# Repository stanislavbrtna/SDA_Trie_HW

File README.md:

# SDA Trié Hardware Sources
Trié is third iteration of the SDA design, it tries to merge the form factor of Sony Clié V-body and phone functionality of the Palm Treo devices, so Trié. In the pcb directory are KiCad project files for the Boards used in the SDA. In the case Directory there are FreeCAD files for the SDA case. You can find more info about the SDA Project on its [project page](https://hackaday.io/project/35165-sda-the-best-new-pda) on hackaday.io.

This design is work-in-progress.

## Known Bugs

## Case notes

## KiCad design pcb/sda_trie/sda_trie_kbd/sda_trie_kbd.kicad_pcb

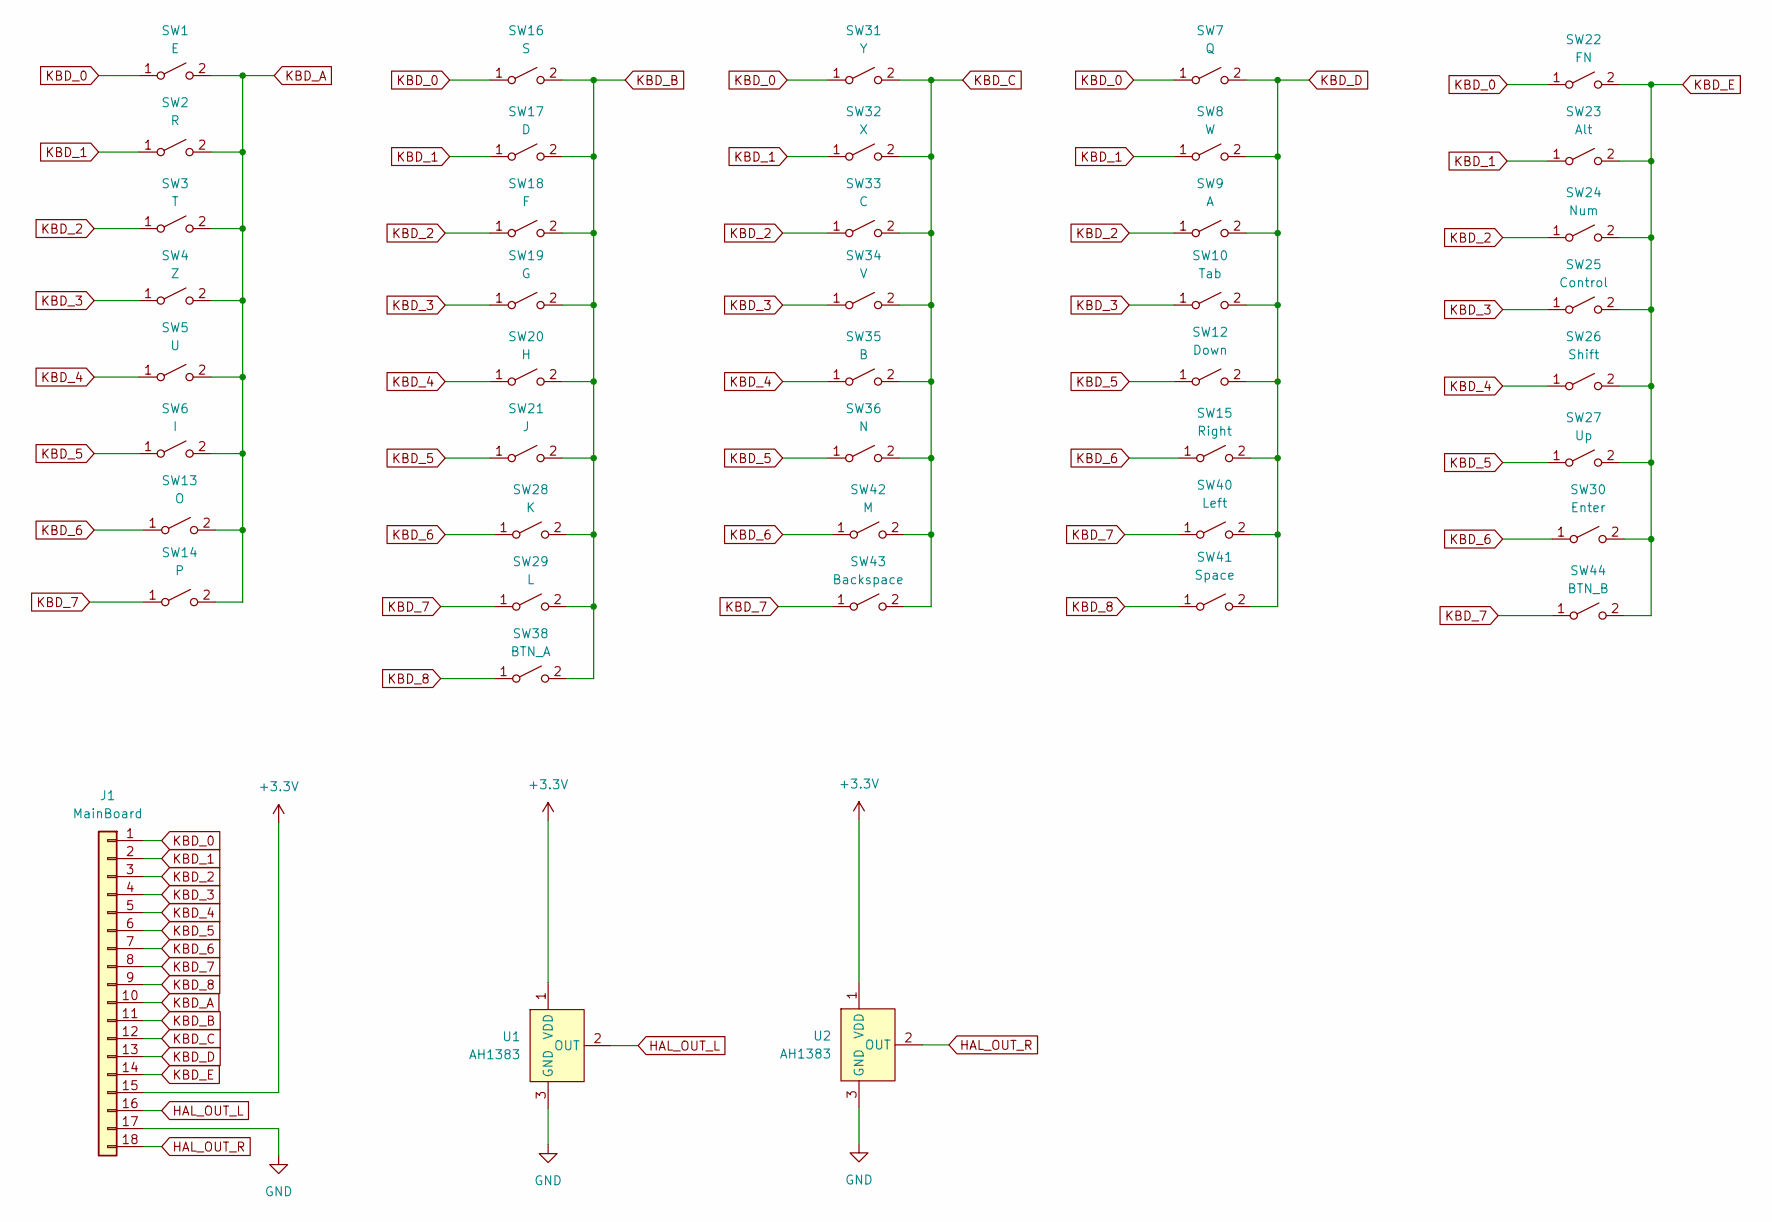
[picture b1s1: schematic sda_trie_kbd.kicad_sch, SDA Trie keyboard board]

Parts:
J1: MainBoard; TE_1-1734839-8_1x18-1MP_P0.5mm_Horizontal
SW1: E; TACT_4MM
SW2: R; TACT_4MM
SW3: T; TACT_4MM
SW4: Z; TACT_4MM
SW5: U; TACT_4MM
SW6: I; TACT_4MM
SW7: Q; TACT_4MM
SW8: W; TACT_4MM
SW9: A; TACT_4MM
SW10: Tab; TACT_4MM
SW12: Down; TACT_4MM
SW13: O; TACT_4MM
SW14: P; TACT_4MM
SW15: Right; TACT_4MM
SW16: S; TACT_4MM
SW17: D; TACT_4MM
SW18: F; TACT_4MM
SW19: G; TACT_4MM
SW20: H; TACT_4MM
SW21: J; TACT_4MM
SW22: FN; TACT_4MM
SW23: Alt; TACT_4MM
SW24: Num; TACT_4MM
SW25: Control; TACT_4MM
SW26: Shift; TACT_4MM
SW27: Up; TACT_4MM
SW28: K; TACT_4MM
SW29: L; TACT_4MM
SW30: Enter; TACT_4MM
SW31: Y; TACT_4MM
SW32: X; TACT_4MM
SW33: C; TACT_4MM
SW34: V; TACT_4MM
SW35: B; TACT_4MM
SW36: N; TACT_4MM
SW38: BTN_A; TACT_4MM
SW40: Left; TACT_4MM
SW41: Space; TACT_4MM
SW42: M; TACT_4MM
SW43: Backspace; TACT_4MM
SW44: BTN_B; TACT_4MM
U1, U2: AH1383; SOT-23

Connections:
+3.3V: J1.15, U1.1 (VDD), U2.1 (VDD)
GND: J1.17, U1.3 (GND), U2.3 (GND)
HAL_OUT_L: J1.16, U1.2 (OUT)
HAL_OUT_R: J1.18, U2.2 (OUT)
KBD_0: J1.1, SW1.1 (A), SW7.1 (A), SW16.1 (A), SW22.1 (A), SW31.1 (A)
KBD_1: J1.2, SW2.1 (A), SW8.1 (A), SW17.1 (A), SW23.1 (A), SW32.1 (A)
KBD_2: J1.3, SW3.1 (A), SW9.1 (A), SW18.1 (A), SW24.1 (A), SW33.1 (A)
KBD_3: J1.4, SW4.1 (A), SW10.1 (A), SW19.1 (A), SW25.1 (A), SW34.1 (A)
KBD_4: J1.5, SW5.1 (A), SW20.1 (A), SW26.1 (A), SW35.1 (A)
KBD_5: J1.6, SW6.1 (A), SW12.1 (A), SW21.1 (A), SW27.1 (A), SW36.1 (A)
KBD_6: J1.7, SW13.1 (A), SW15.1 (A), SW28.1 (A), SW30.1 (A), SW42.1 (A)
KBD_7: J1.8, SW14.1 (A), SW29.1 (A), SW40.1 (A), SW43.1 (A), SW44.1 (A)
KBD_8: J1.9, SW38.1 (A), SW41.1 (A)
KBD_A: J1.10, SW1.2 (B), SW2.2 (B), SW3.2 (B), SW4.2 (B), SW5.2 (B), SW6.2 (B), SW13.2 (B), SW14.2 (B)
KBD_B: J1.11, SW16.2 (B), SW17.2 (B), SW18.2 (B), SW19.2 (B), SW20.2 (B), SW21.2 (B), SW28.2 (B), SW29.2 (B), SW38.2 (B)
KBD_C: J1.12, SW31.2 (B), SW32.2 (B), SW33.2 (B), SW34.2 (B), SW35.2 (B), SW36.2 (B), SW42.2 (B), SW43.2 (B)
KBD_D: J1.13, SW7.2 (B), SW8.2 (B), SW9.2 (B), SW10.2 (B), SW12.2 (B), SW15.2 (B), SW40.2 (B), SW41.2 (B)
KBD_E: J1.14, SW22.2 (B), SW23.2 (B), SW24.2 (B), SW25.2 (B), SW26.2 (B), SW27.2 (B), SW30.2 (B), SW44.2 (B)

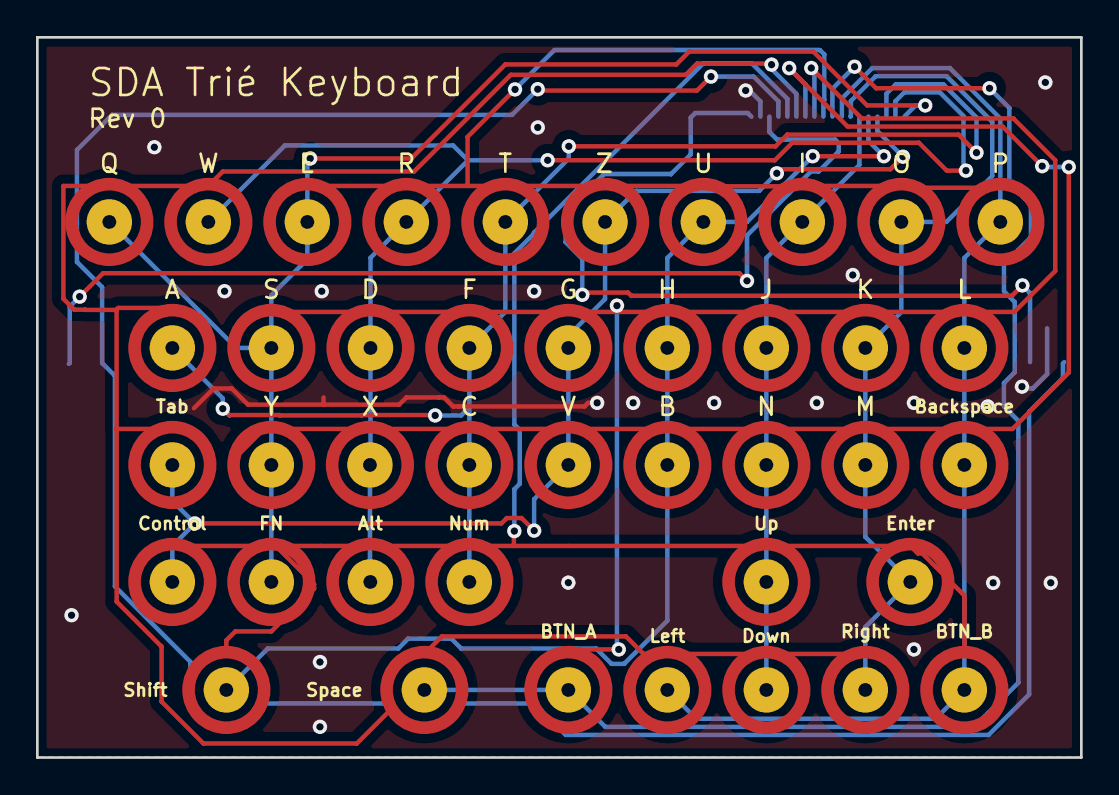
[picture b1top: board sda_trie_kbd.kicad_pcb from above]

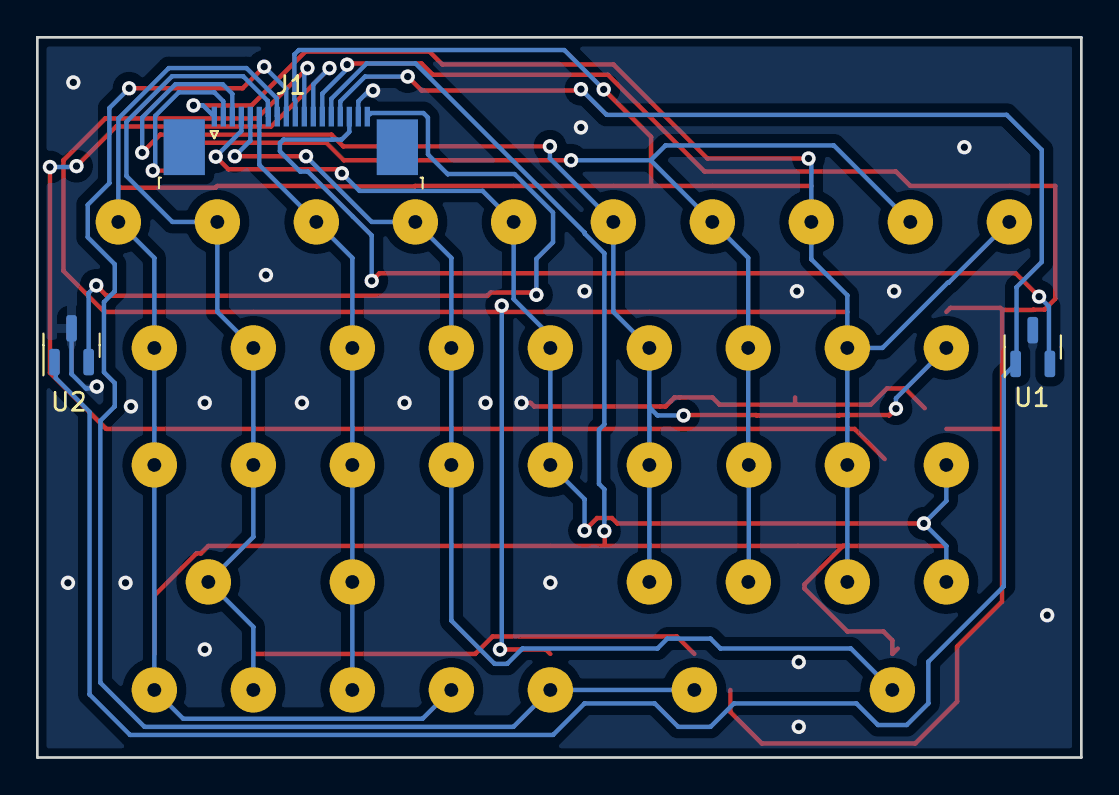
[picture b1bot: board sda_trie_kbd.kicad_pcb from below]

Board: 2 copper layers, 58.0 x 40.0 mm, 44 parts (3 on the bottom side), 18 nets.

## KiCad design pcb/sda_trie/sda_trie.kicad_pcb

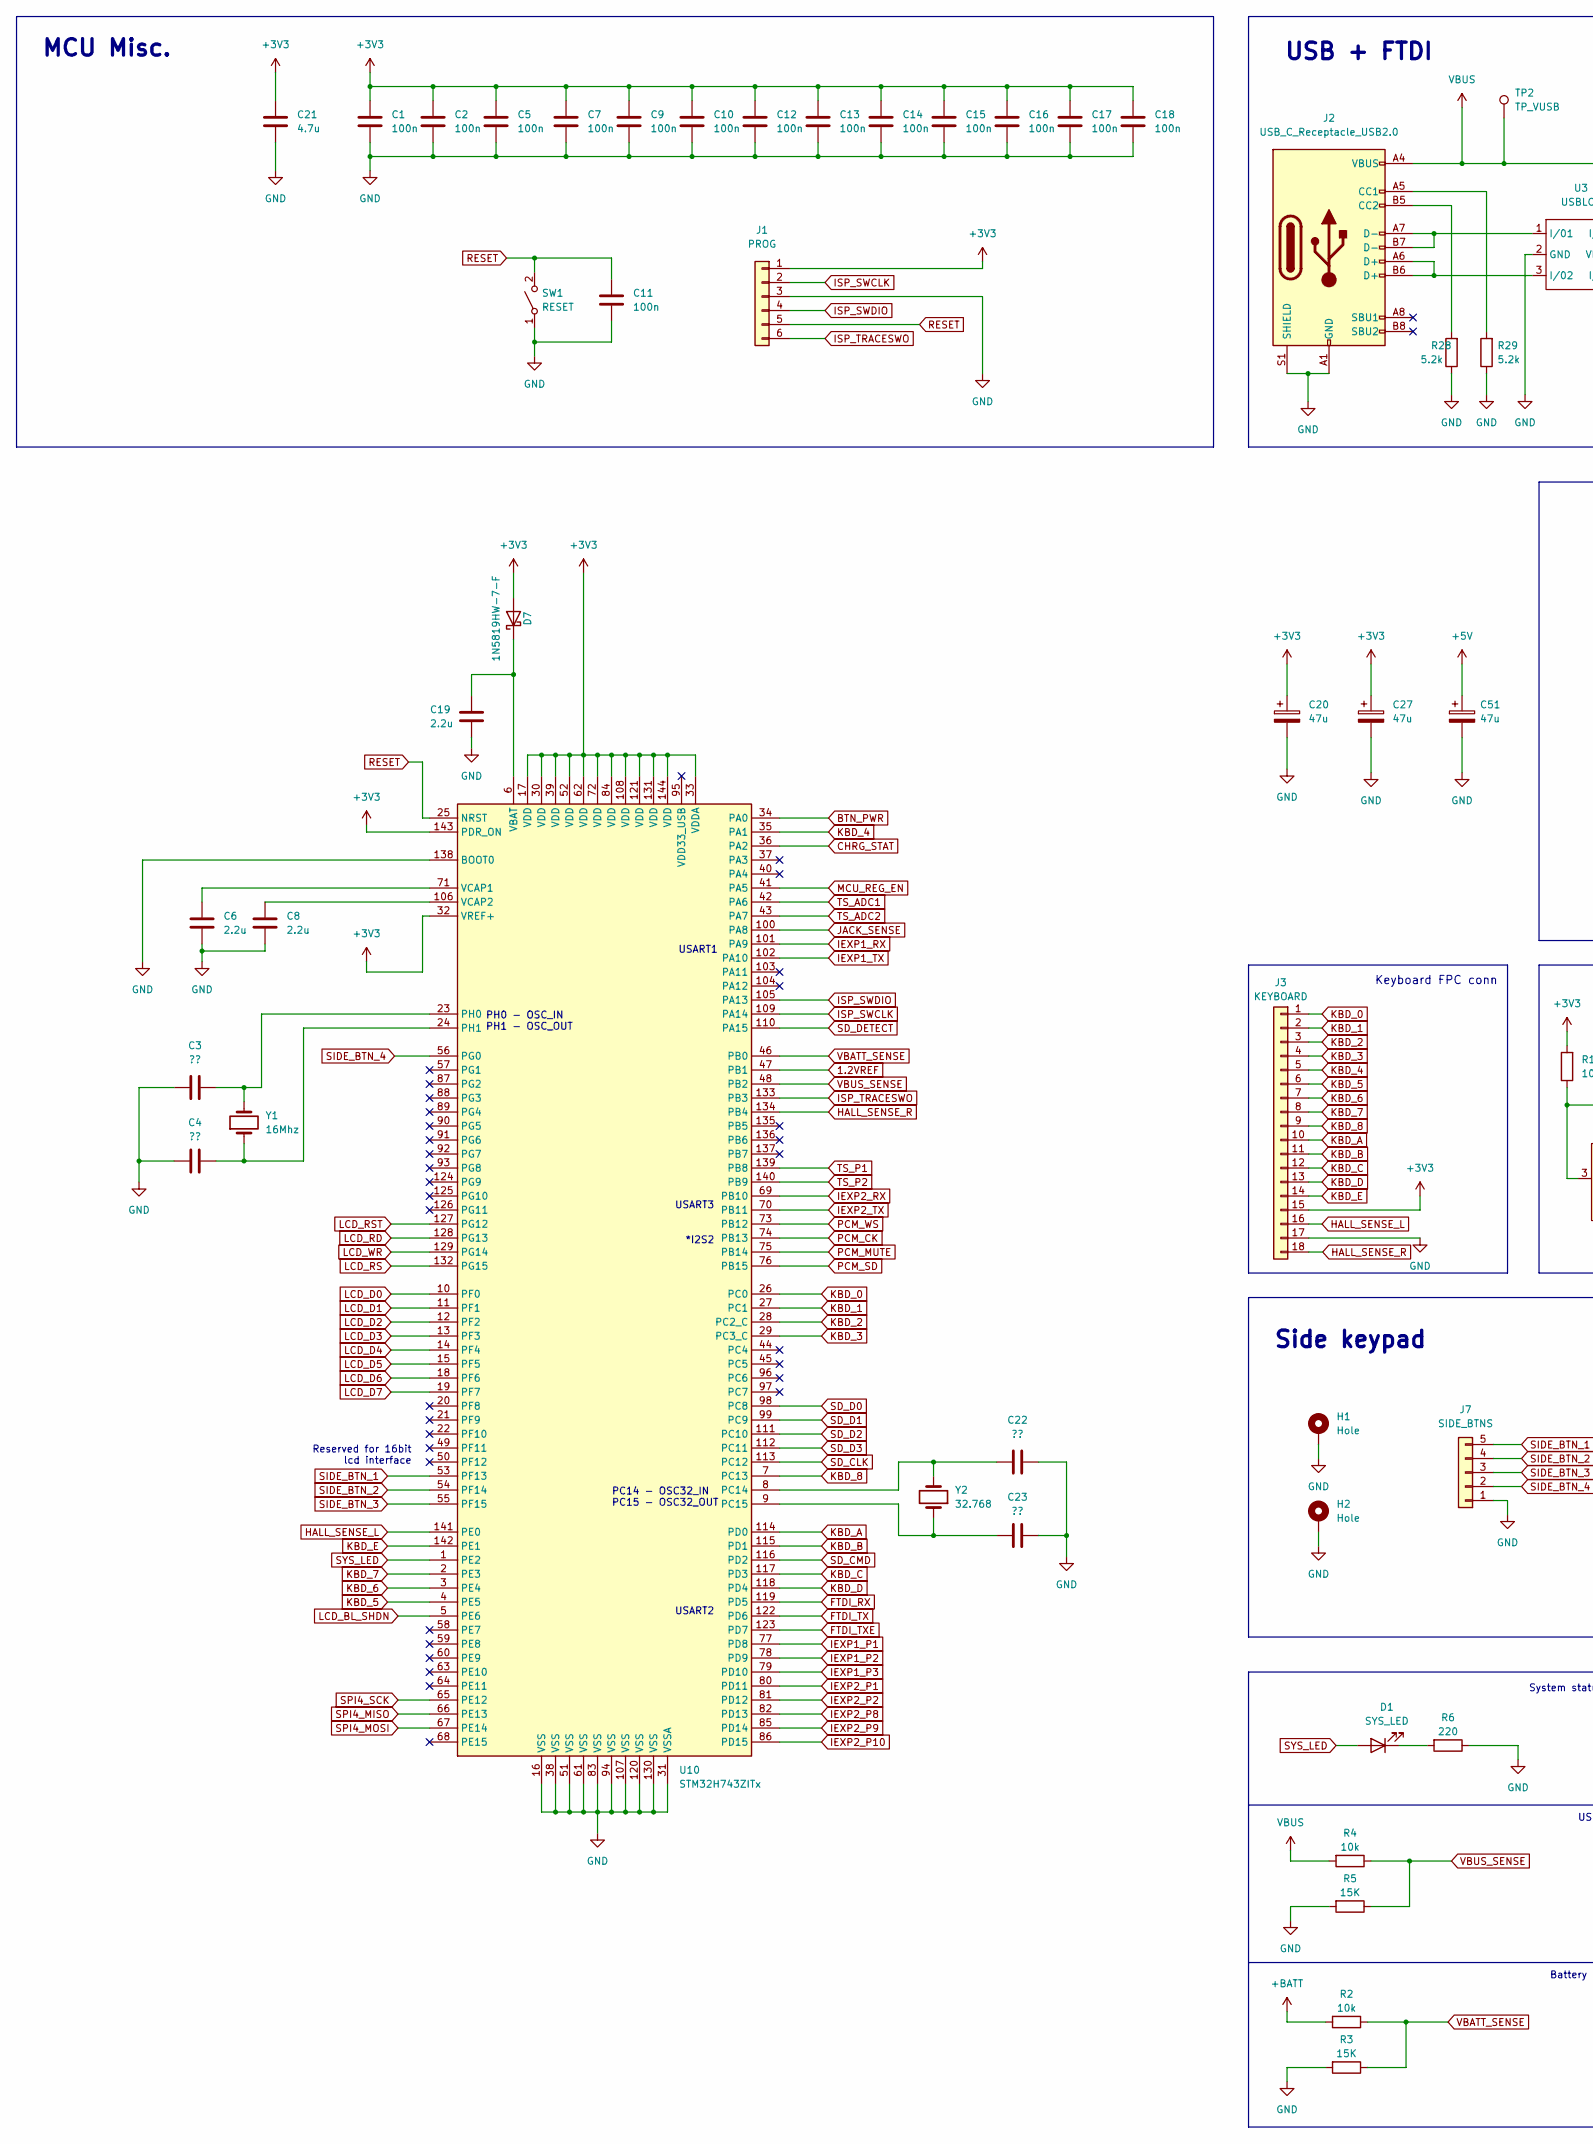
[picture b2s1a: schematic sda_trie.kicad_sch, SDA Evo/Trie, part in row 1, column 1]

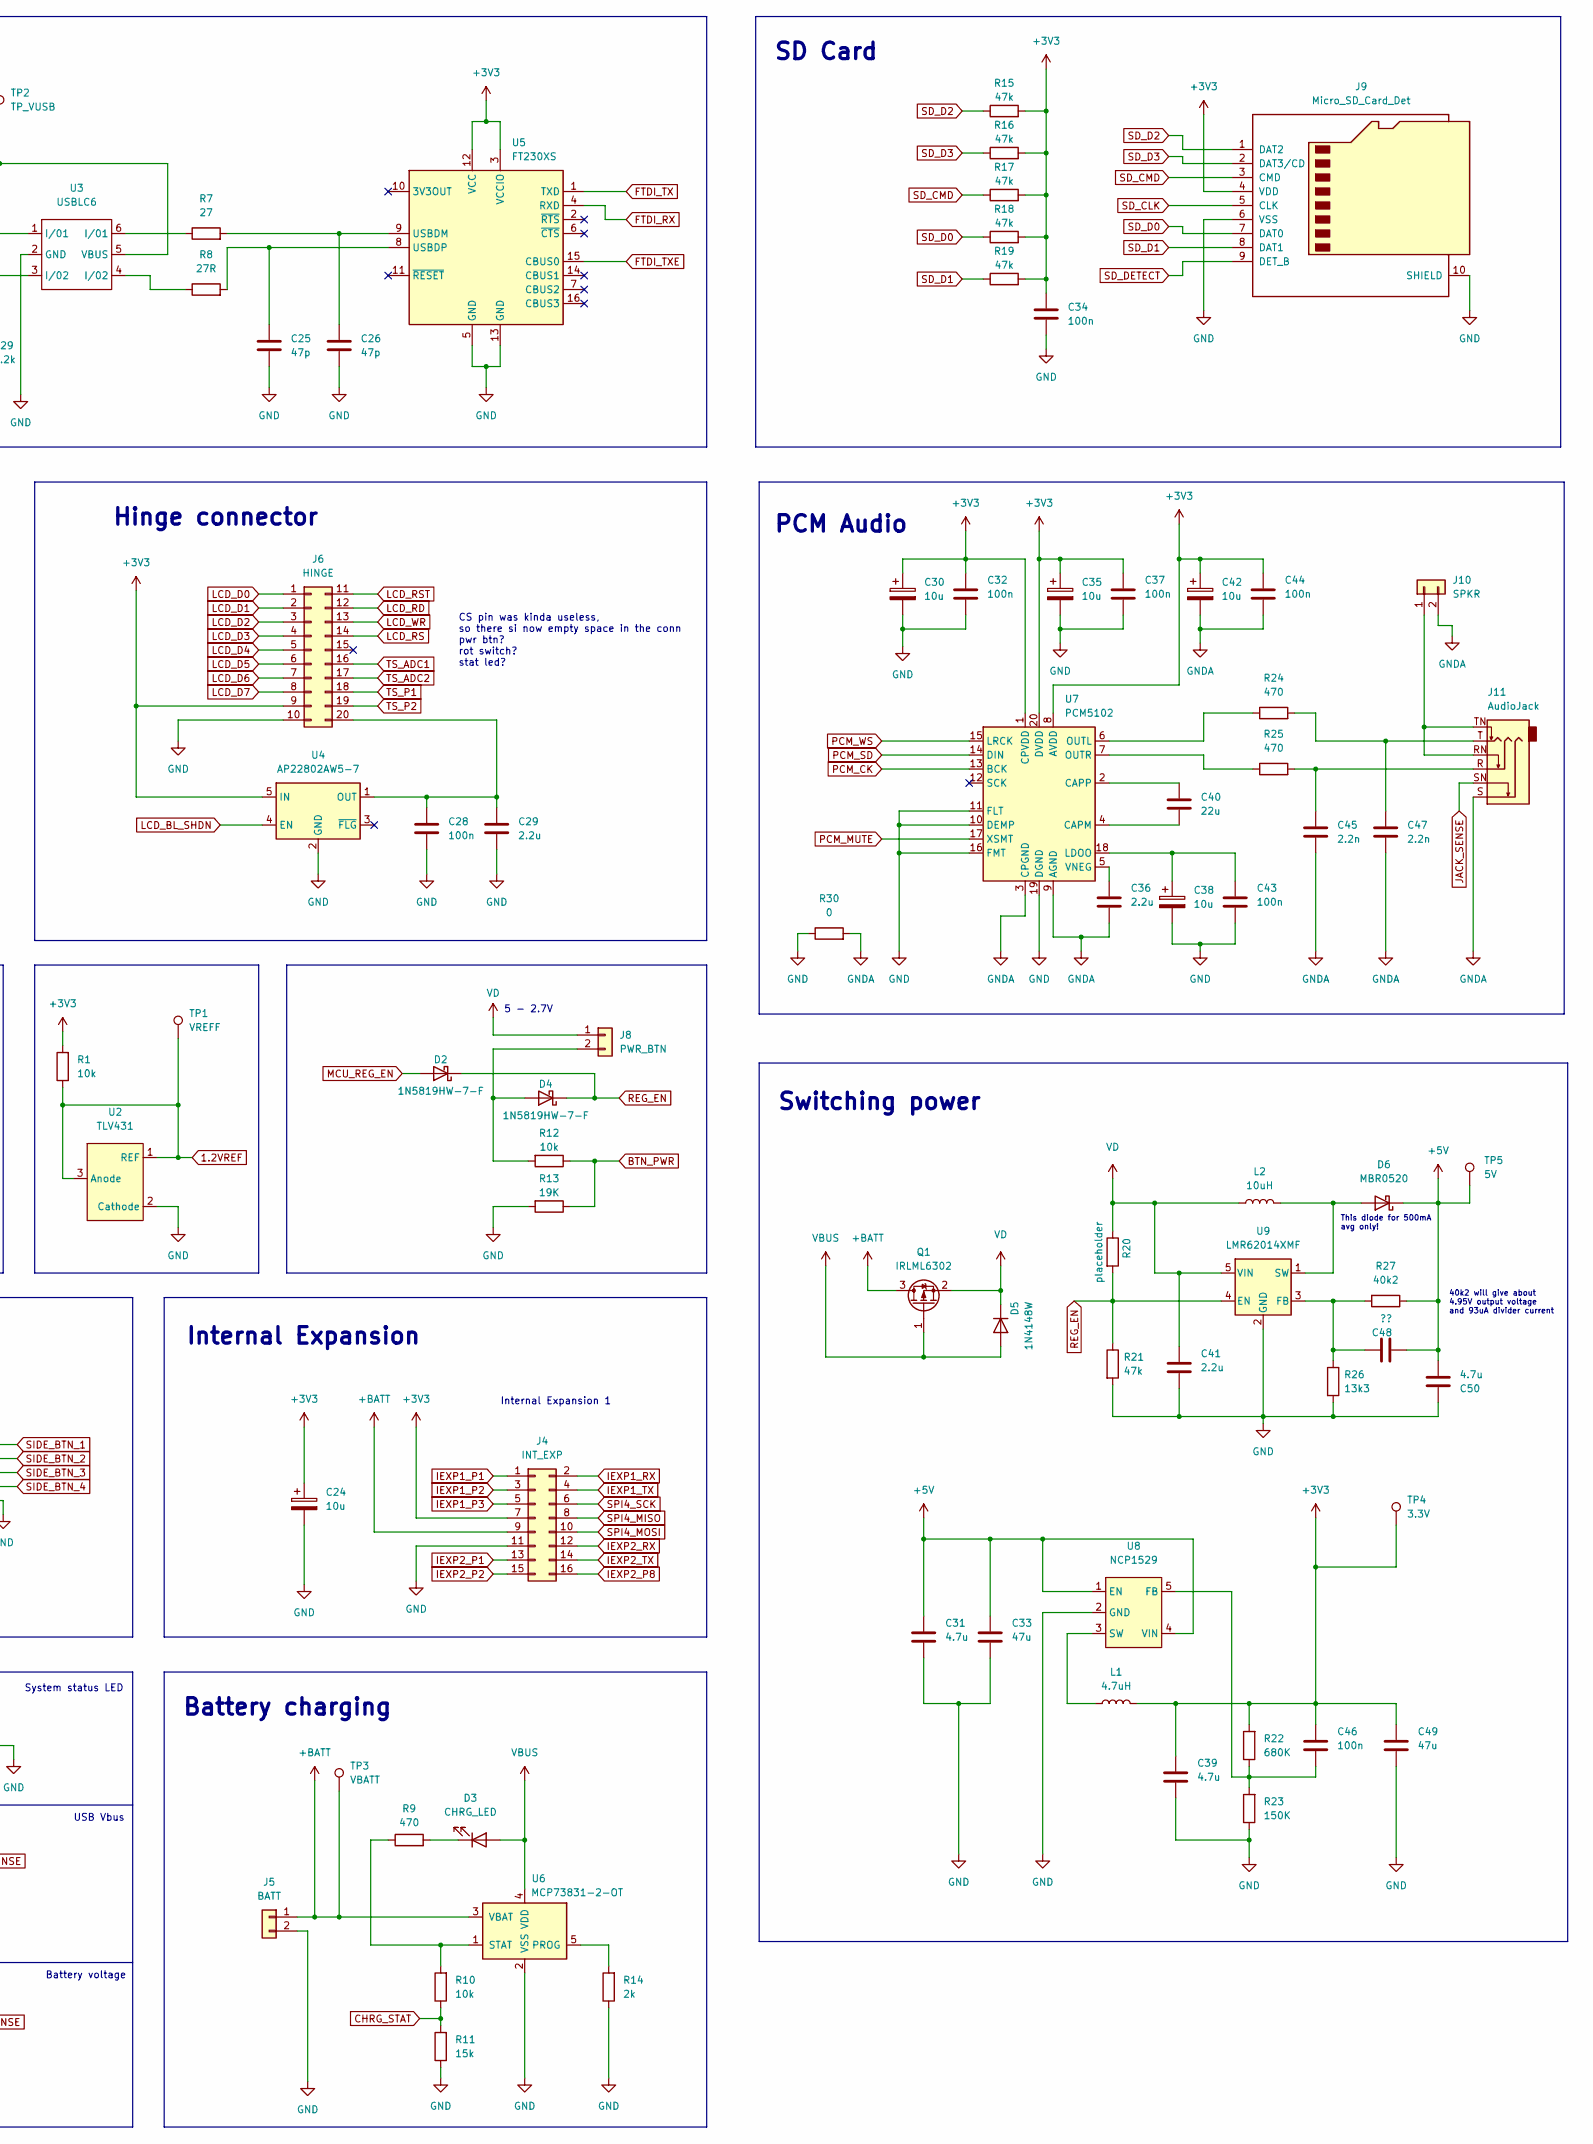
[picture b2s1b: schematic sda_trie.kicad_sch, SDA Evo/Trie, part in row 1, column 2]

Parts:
C1, C2, C5, C7, C9, C10, C11, C12, C13, C14, C15, C16, C17, C18, C28, C32, C34, C37, C43, C44, C46: 100n; C_0805_2012Metric_Pad1.18x1.45mm_HandSolder
C3, C4, C22, C23, C48: ??; C_0805_2012Metric_Pad1.18x1.45mm_HandSolder
C6, C8, C19, C29, C36, C41: 2.2u; C_0805_2012Metric_Pad1.18x1.45mm_HandSolder
C20, C27, C51: 47u; CP_EIA-7343-15_Kemet-W_Pad2.25x2.55mm_HandSolder
C21, C31, C39, C50: 4.7u; C_0805_2012Metric_Pad1.18x1.45mm_HandSolder
C24, C30, C35, C38, C42: 10u; C_0805_2012Metric_Pad1.18x1.45mm_HandSolder
C25, C26: 47p; C_0805_2012Metric_Pad1.18x1.45mm_HandSolder
C33, C49: 47u; C_0805_2012Metric_Pad1.18x1.45mm_HandSolder
C40: 22u; C_0805_2012Metric_Pad1.18x1.45mm_HandSolder
C45, C47: 2.2n; C_0805_2012Metric_Pad1.18x1.45mm_HandSolder
D1: SYS_LED; LED_D3.0mm_FlatTop
D2, D4, D7: 1N5819HW-7-F; D_SOD-123
D3: CHRG_LED; LED_D3.0mm_FlatTop
D5: 1N4148W; D_SOD-123
D6: MBR0520; D_SOD-123
H1, H2: Hole; Mounting_Wuerth_WA-SMSI-M1.6_H1.5mm_9774015633
J1: PROG; PinHeader_1x06_P1.00mm_Vertical
J2: USB_C_Receptacle_USB2.0; USB_C_Receptacle_XKB_U262-16XN-4BVC11
J3: KEYBOARD; TE_1-1734839-8_1x18-1MP_P0.5mm_Horizontal
J4: INT_EXP; PinHeader_2x08_P1.00mm_Vertical_SMD
J5: BATT; PinHeader_1x02_P2.54mm_Horizontal
J6: HINGE; PinHeader_2x10_P1.00mm_Horizontal
J7: SIDE_BTNS; PinHeader_1x05_P1.00mm_Horizontal
J8: PWR_BTN; PinHeader_1x02_P1.00mm_Vertical
J9: Micro_SD_Card_Det; SD-Connector
J10: SPKR; PinHeader_1x02_P1.00mm_Vertical
J11: AudioJack; 3.5 Jack
L1: 4.7uH; HCM1A4020V2
L2: 10uH; SDN0530MT100
Q1: IRLML6302; SOT-23
R1, R2, R4, R10, R12: 10k; R_0805_2012Metric_Pad1.20x1.40mm_HandSolder
R3, R5: 15K; R_0805_2012Metric_Pad1.20x1.40mm_HandSolder
R6: 220; R_0805_2012Metric_Pad1.20x1.40mm_HandSolder
R7: 27; R_0805_2012Metric_Pad1.20x1.40mm_HandSolder
R8: 27R; R_0805_2012Metric_Pad1.20x1.40mm_HandSolder
R9, R24, R25: 470; R_0805_2012Metric_Pad1.20x1.40mm_HandSolder
R11: 15k; R_0805_2012Metric_Pad1.20x1.40mm_HandSolder
R13: 19K; R_0805_2012Metric_Pad1.20x1.40mm_HandSolder
R14: 2k; R_0805_2012Metric_Pad1.20x1.40mm_HandSolder
R15, R16, R17, R18, R19, R21: 47k; R_0805_2012Metric_Pad1.20x1.40mm_HandSolder
R20: placeholder; R_0805_2012Metric_Pad1.20x1.40mm_HandSolder
R22: 680K; R_0805_2012Metric_Pad1.20x1.40mm_HandSolder
R23: 150K; R_0805_2012Metric_Pad1.20x1.40mm_HandSolder
R26: 13k3; R_0805_2012Metric_Pad1.20x1.40mm_HandSolder
R27: 40k2; R_0805_2012Metric_Pad1.20x1.40mm_HandSolder
R28, R29: 5.2k; R_0805_2012Metric_Pad1.20x1.40mm_HandSolder
R30: 0; R_0805_2012Metric_Pad1.20x1.40mm_HandSolder
SW1: RESET; SW_SPST_B3S-1000
TP1: VREFF; TestPoint_Pad_D1.0mm
TP2: TP_VUSB; TestPoint_Pad_D1.0mm
TP3: VBATT; TestPoint_Pad_D1.0mm
TP4: 3.3V; TestPoint_Pad_D1.0mm
TP5: 5V; TestPoint_Pad_D1.0mm
U2: TLV431; TSOT-23
U3: USBLC6; TSOT-23-6_HandSoldering
U4: AP22802AW5-7; SOT-23-5_HandSoldering
U5: FT230XS; SSOP-16_3.9x4.9mm_P0.635mm
U6: MCP73831-2-OT; SOT-23-5_HandSoldering
U7: PCM5102; TSSOP-20_4.4x6.5mm_P0.65mm
U8: NCP1529; TSOT-23-5_HandSoldering
U9: LMR62014XMF; SOT-23-5_HandSoldering
U10: STM32H743ZITx; LQFP-144_20x20mm_P0.5mm
Y1: 16Mhz; SMDXT224
Y2: 32.768; 32.768K-85SMXR

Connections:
1.2VREF: R1.1, TP1.1, U2.1 (REF), U2.3 (Anode), U10.47 (PB1)
+3V3: C1.1, C2.1, C5.1, C7.1, C9.1, C10.1, C12.1, C13.1, C14.1, C15.1, C16.1, C17.1, C18.1, C20.1, C21.1, C24.1, C27.1, C30.1, C32.1, C34.1, C35.1, C37.1, C39.1, C42.1, C44.1, C46.1, C49.1, D7.2 (A), J1.1, J3.15, J4.7, J6.9, J9.4 (VDD), L1.2, R1.2, R15.2, R16.2, R17.2, R18.2, R19.2, R22.2, TP4.1, U4.5 (IN), U5.3 (VCCIO), U5.12 (VCC), U7.1 (CPVDD), U7.8 (AVDD), U7.20 (DVDD), U10.17 (VDD), U10.30 (VDD), U10.32 (VREF+), U10.33 (VDDA), U10.39 (VDD), U10.52 (VDD), U10.62 (VDD), U10.72 (VDD), U10.84 (VDD), U10.108 (VDD), U10.121 (VDD), U10.131 (VDD), U10.143 (PDR_ON), U10.144 (VDD)
+5V: C31.1, C33.1, C48.2, C50.1, C51.1, D6.1 (K), R27.1, TP5.1, U8.1 (EN), U8.4 (VIN)
+BATT: J4.9, J5.1, Q1.3 (D), R2.2, TP3.1, U6.3 (VBAT)
BTN_PWR: R12.1, R13.1, U10.34 (PA0)
CHRG_STAT: R10.1, R11.2, U10.36 (PA2)
FTDI_RX: U5.4 (RXD), U10.119 (PD5)
FTDI_TX: U5.1 (TXD), U10.122 (PD6)
FTDI_TXE: U5.15 (CBUS0), U10.123 (PD7)
GND: C1.2, C2.2, C3.1, C4.1, C5.2, C6.2, C7.2, C8.2, C9.2, C10.2, C11.2, C12.2, C13.2, C14.2, C15.2, C16.2, C17.2, C18.2, C19.2, C20.2, C21.2, C22.1, C23.1, C24.2, C25.2, C26.2, C27.2, C28.2, C29.2, C30.2, C31.2, C32.2, C33.2, C34.2, C35.2, C37.2, C38.2, C39.2, C41.2, C43.2, C49.2, C50.2, C51.2, H1.1, H2.1, J1.3, J2.A1 (GND), J2.A12 (GND), J2.B1 (GND), J2.B12 (GND), J2.S1 (SHIELD), J3.17, J4.11, J5.2, J6.10, J7.1, J9.6 (VSS), J9.10 (SHIELD), R3.2, R5.2, R6.1, R11.1, R13.2, R14.1, R21.2, R23.1, R26.2, R28.1, R29.1, R30.1, SW1.1 (A), U2.2 (Cathode), U3.2 (GND), U4.2 (GND), U5.5 (GND), U5.13 (GND), U6.2 (VSS), U7.10 (DEMP), U7.11 (FLT), U7.16 (FMT), U7.19 (DGND), U8.2 (GND), U9.2 (GND), U10.16 (VSS), U10.31 (VSSA), U10.38 (VSS), U10.51 (VSS), U10.61 (VSS), U10.83 (VSS), U10.94 (VSS), U10.107 (VSS), U10.120 (VSS), U10.130 (VSS), U10.138 (BOOT0)
GNDA: C36.2, C42.2, C44.2, C45.2, C47.2, J10.2, J11.S, R30.2, U7.3 (CPGND), U7.9 (AGND)
HALL_SENSE_L: J3.16, U10.141 (PE0)
HALL_SENSE_R: J3.18, U10.134 (PB4)
IEXP1_P1: J4.1, U10.77 (PD8)
IEXP1_P2: J4.3, U10.78 (PD9)
IEXP1_P3: J4.5, U10.79 (PD10)
IEXP1_RX: J4.2, U10.101 (PA9)
IEXP1_TX: J4.4, U10.102 (PA10)
IEXP2_P1: J4.13, U10.80 (PD11)
IEXP2_P2: J4.15, U10.81 (PD12)
IEXP2_P8: J4.16, U10.82 (PD13)
IEXP2_P9: U10.85 (PD14)
IEXP2_P10: U10.86 (PD15)
IEXP2_RX: J4.12, U10.69 (PB10)
IEXP2_TX: J4.14, U10.70 (PB11)
ISP_SWCLK: J1.2, U10.109 (PA14)
ISP_SWDIO: J1.4, U10.105 (PA13)
ISP_TRACESWO: J1.6, U10.133 (PB3)
JACK_SENSE: J11.SN, U10.100 (PA8)
KBD_0: J3.1, U10.26 (PC0)
KBD_1: J3.2, U10.27 (PC1)
KBD_2: J3.3, U10.28 (PC2_C)
KBD_3: J3.4, U10.29 (PC3_C)
KBD_4: J3.5, U10.35 (PA1)
KBD_5: J3.6, U10.4 (PE5)
KBD_6: J3.7, U10.3 (PE4)
KBD_7: J3.8, U10.2 (PE3)
KBD_8: J3.9, U10.7 (PC13)
KBD_A: J3.10, U10.114 (PD0)
KBD_B: J3.11, U10.115 (PD1)
KBD_C: J3.12, U10.117 (PD3)
KBD_D: J3.13, U10.118 (PD4)
KBD_E: J3.14, U10.142 (PE1)
LCD_BL_SHDN: U4.4 (EN), U10.5 (PE6)
LCD_D0: J6.1, U10.10 (PF0)
LCD_D1: J6.2, U10.11 (PF1)
LCD_D2: J6.3, U10.12 (PF2)
LCD_D3: J6.4, U10.13 (PF3)
LCD_D4: J6.5, U10.14 (PF4)
LCD_D5: J6.6, U10.15 (PF5)
LCD_D6: J6.7, U10.18 (PF6)
LCD_D7: J6.8, U10.19 (PF7)
LCD_RD: J6.12, U10.128 (PG13)
LCD_RS: J6.14, U10.132 (PG15)
LCD_RST: J6.11, U10.127 (PG12)
LCD_WR: J6.13, U10.129 (PG14)
MCU_REG_EN: D2.2 (A), U10.41 (PA5)
unnamed: C3.2, U10.23 (PH0), Y1.2
unnamed: C4.2, U10.24 (PH1), Y1.1
unnamed: C6.1, U10.71 (VCAP1)
unnamed: C8.1, U10.106 (VCAP2)
unnamed: C19.1, D7.1 (K), U10.6 (VBAT)
unnamed: C22.2, U10.8 (PC14), Y2.2
unnamed: C23.2, U10.9 (PC15), Y2.1
unnamed: C25.1, R8.2, U5.8 (USBDP)
unnamed: C26.1, R7.2, U5.9 (USBDM)
unnamed: C28.1, C29.1, J6.20, U4.1 (OUT)
unnamed: C36.1, U7.5 (VNEG)
unnamed: C38.1, C43.1, U7.18 (LDOO)
unnamed: C40.1, U7.2 (CAPP)
unnamed: C40.2, U7.4 (CAPM)
unnamed: C45.1, J11.R, R25.2
unnamed: C46.2, R22.1, R23.2, U8.5 (FB)
unnamed: C47.1, J11.T, R24.2
unnamed: C48.1, R26.1, R27.2, U9.3 (FB)
unnamed: D1.1 (K), R6.2
unnamed: D3.1 (K), R9.2
unnamed: D4.2 (A), J8.2, R12.2
unnamed: D6.2 (A), L2.2, U9.1 (SW)
unnamed: J2.A5 (CC1), R29.2
unnamed: J2.A6 (D+), J2.B6 (D+), U3.3 (I/02)
unnamed: J2.A7 (D-), J2.B7 (D-), U3.1 (I/01)
unnamed: J2.B5 (CC2), R28.2
unnamed: J10.1, J11.RN, J11.TN
unnamed: L1.1, U8.3 (SW)
unnamed: R7.1, U3.6 (I/01)
unnamed: R8.1, U3.4 (I/02)
unnamed: R9.1, R10.2, U6.1 (STAT)
unnamed: R14.2, U6.5 (PROG)
unnamed: R24.1, U7.6 (OUTL)
unnamed: R25.1, U7.7 (OUTR)
PCM_CK: U7.13 (BCK), U10.74 (PB13)
PCM_MUTE: U7.17 (XSMT), U10.75 (PB14)
PCM_SD: U7.14 (DIN), U10.76 (PB15)
PCM_WS: U7.15 (LRCK), U10.73 (PB12)
REG_EN: D2.1 (K), D4.1 (K), R20.2, R21.1, U9.4 (EN)
RESET: C11.1, J1.5, SW1.2 (B), U10.25 (NRST)
SD_CLK: J9.5 (CLK), U10.113 (PC12)
SD_CMD: J9.3 (CMD), R17.1, U10.116 (PD2)
SD_D0: J9.7 (DAT0), R18.1, U10.98 (PC8)
SD_D1: J9.8 (DAT1), R19.1, U10.99 (PC9)
SD_D2: J9.1 (DAT2), R15.1, U10.111 (PC10)
SD_D3: J9.2 (DAT3/CD), R16.1, U10.112 (PC11)
SD_DETECT: J9.9 (DET_B), U10.110 (PA15)
SIDE_BTN_1: J7.5, U10.53 (PF13)
SIDE_BTN_2: J7.4, U10.54 (PF14)
SIDE_BTN_3: J7.3, U10.55 (PF15)
SIDE_BTN_4: J7.2, U10.56 (PG0)
SPI4_MISO: J4.8, U10.66 (PE13)
SPI4_MOSI: J4.10, U10.67 (PE14)
SPI4_SCK: J4.6, U10.65 (PE12)
SYS_LED: D1.2 (A), U10.1 (PE2)
TS_ADC1: J6.16, U10.42 (PA6)
TS_ADC2: J6.17, U10.43 (PA7)
TS_P1: J6.18, U10.139 (PB8)
TS_P2: J6.19, U10.140 (PB9)
VBATT_SENSE: R2.1, R3.1, U10.46 (PB0)
VBUS: D3.2 (A), D5.2 (A), J2.A4 (VBUS), J2.A9 (VBUS), J2.B4 (VBUS), J2.B9 (VBUS), Q1.1 (G), R4.2, TP2.1, U3.5 (VBUS), U6.4 (VDD)
VBUS_SENSE: R4.1, R5.1, U10.48 (PB2)
VD: C41.1, D5.1 (K), J8.1, L2.1, Q1.2 (S), R20.1, U9.5 (VIN)

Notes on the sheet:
MCU Misc.
Battery voltage
USART1
*I2S2
Internal Expansion 1
40k2 will give about 4.95V output voltage and 93uA divider current
Internal Expansion
USART2
USB + FTDI
SD Card
System status LED
USART3
PCM Audio
Keyboard FPC conn
5 - 2.7V
PH0 - OSC_IN PH1 - OSC_OUT
Reserved for 16bit lcd interface
CS pin was kinda useless, so there si now empty space in the conn pwr btn? rot switch? stat led?
Switching power
Hinge connector
This diode for 500mA avg only!
Side keypad
USB Vbus
PC14 - OSC32_IN PC15 - OSC32_OUT
Battery charging

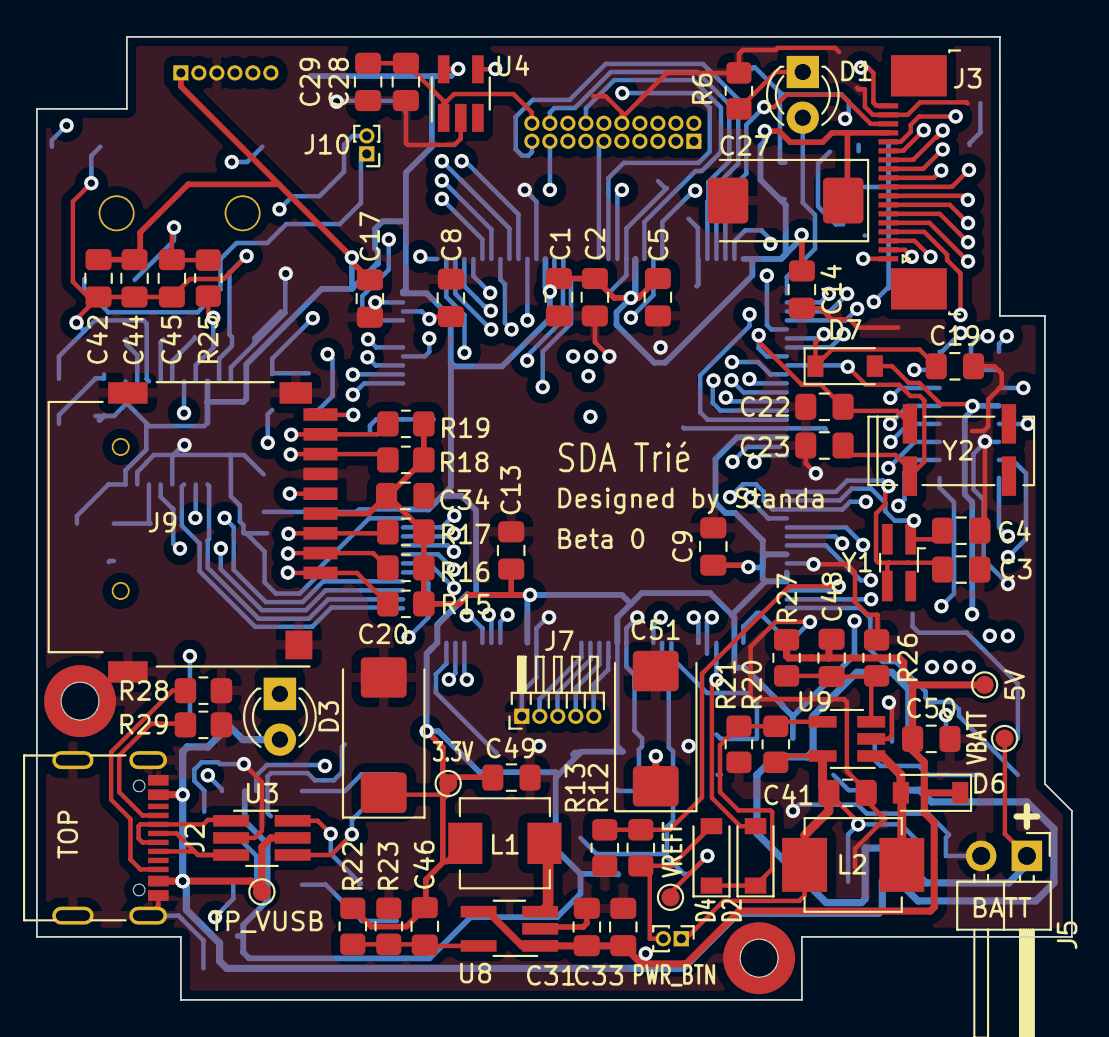
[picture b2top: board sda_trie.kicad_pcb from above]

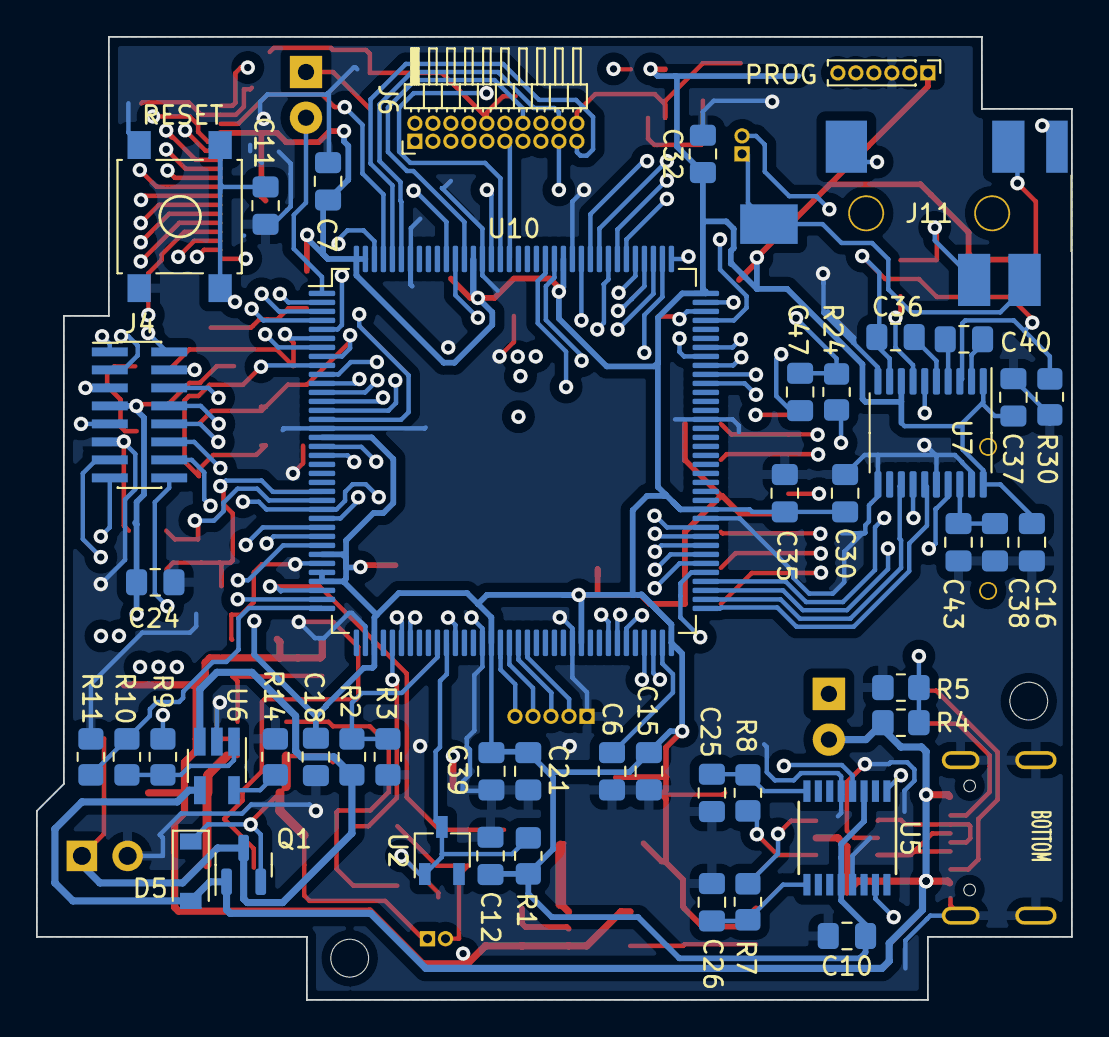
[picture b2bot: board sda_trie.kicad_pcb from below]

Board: 4 copper layers, 57.5 x 53.5 mm, 121 parts (47 on the bottom side), 118 nets.

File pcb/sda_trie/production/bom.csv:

Designator,Footprint,Quantity,Value,LCSC Part #
C1,0805,1,100n,
C10,0805,1,100n,
C11,0805,1,100n,
C12,0805,1,100n,
C13,0805,1,100n,
C14,0805,1,100n,
C15,0805,1,100n,
C16,0805,1,100n,
C17,0805,1,100n,
C18,0805,1,100n,
C19,0805,1,2.2u,
C2,0805,1,100n,
C21,0805,1,4.7u,
C22,0805,1,??,
C23,0805,1,??,
C24,0805,1,10u,
C25,0805,1,47p,
C26,0805,1,47p,
C27,0805,1,10u,
C28,0805,1,100n,
C29,0805,1,2.2u,
C3,0805,1,??,
C30,0805,1,10u,
C31,0805,1,4.7u,
C32,0805,1,100n,
C33,0805,1,47u,
C34,0805,1,100n,
C35,0805,1,10u,
C36,0805,1,2.2u,
C37,0805,1,100n,
C38,0805,1,10u,
C39,0805,1,4.7u,
C4,0805,1,??,
C40,0805,1,22u,
C41,0805,1,2.2u,
C42,0805,1,10u,
C43,0805,1,100n,
C44,0805,1,100n,
C45,0805,1,2.2n,
C46,0805,1,100n,
C47,0805,1,2.2n,
C48,0805,1,??,
C49,0805,1,47u,
C5,0805,1,100n,
C50,0805,1,4.7u,
C6,0805,1,2.2u,
C7,0805,1,100n,
C8,0805,1,2.2u,
C9,0805,1,100n,
D1,LED_D3.0mm_FlatTop,1,SYS_LED,
"D2, D4, D7",D_SOD-123,3,1N5819HW-7-F,
D3,LED_D3.0mm_FlatTop,1,CHRG_LED,
D5,D_SOD-123,1,1N4148W,
D6,D_SOD-123,1,MBR0520,
J1,PinHeader_1x06_P1.00mm_Vertical,1,PROG,
J10,PinHeader_1x02_P1.00mm_Vertical,1,SPKR,
J11,3.5 Jack,1,AudioJack,
J2,USB_C_Receptacle_XKB_U262-16XN-4BVC11,1,USB_C_Receptacle_USB2.0,
J3,PinHeader_2x08_P1.00mm_Vertical,1,KEYBOARD,
"J4, J7",PinHeader_2x05_P1.00mm_Vertical_SMD,2,Conn_02x05_Top_Bottom,
J5,PinHeader_1x02_P1.00mm_Horizontal,1,BATT,
J6,PinHeader_2x11_P1.00mm_Horizontal,1,HINGE,
J8,PinHeader_1x02_P1.00mm_Vertical,1,PWR_BTN,
J9,SD-Connector,1,Micro_SD_Card_Det,
L1,HCM1A4020V2,1,4.7uH,
L2,SDN0530MT100,1,10uH,
Q1,SOT-23,1,IRLML6302,
R1,0805,1,10k,
R10,0805,1,10k,
R11,0805,1,15k,
R12,0805,1,10k,
R13,0805,1,19K,
R14,0805,1,2k,
R15,0805,1,47k,
R16,0805,1,47k,
R17,0805,1,47k,
R18,0805,1,47k,
R19,0805,1,47k,
R2,0805,1,10k,
R20,0805,1,placeholder,
R21,0805,1,47k,
R22,0805,1,680K,
R23,0805,1,150K,
R24,0805,1,470,
R25,0805,1,470,
R26,0805,1,13k3,
R27,0805,1,40k2,
R28,0805,1,5.2k,
R29,0805,1,5.2k,
R3,0805,1,15K,
R30,0805,1,0,
R4,0805,1,10k,
R5,0805,1,15K,
R6,0805,1,220,
R7,0805,1,27,
R8,0805,1,27R,
R9,0805,1,470,
SW1,SW_SPST_B3S-1000,1,RESET,
TP1,TestPoint_Pad_D1.0mm,1,VREFF,
TP2,TestPoint_Pad_D1.0mm,1,TP_VUSB,
TP3,TestPoint_Pad_D1.0mm,1,VBATT,
TP4,TestPoint_Pad_D1.0mm,1,3.3V,
TP5,TestPoint_Pad_D1.0mm,1,5V,
U10,LQFP-144_20x20mm_P0.5mm,1,STM32H743ZITx,
U2,TSOT-23,1,TLV431,
U3,TSOT-23-6_HandSoldering,1,USBLC6,
U4,SOT-23-5_HandSoldering,1,AP22802AW5-7,
U5,SSOP-16_3.9x4.9mm_P0.635mm,1,FT230XS,
U6,SOT-23-5_HandSoldering,1,MCP73831-2-OT,
U7,TSSOP-20_4.4x6.5mm_P0.65mm,1,PCM5102,
U8,TSOT-23-5_HandSoldering,1,NCP1529,
U9,SOT-23-5_HandSoldering,1,LMR62014XMF,
Y1,SMDXT224,1,16Mhz,
Y2,32.768K-85SMXR,1,32.768,
